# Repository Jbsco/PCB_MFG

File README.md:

# PCB_MFG

This repository was created for working with and improving the on-campus PCB design and production process using open-source software resources as well as physical resources and space provided by the University of Colorado Boulder and Colorado Mesa University Partnership Program on the Colorado Mesa University campus. These resources are made available to students and faculty alike.

## Introduction

PCB production is in the process of being made more accessible to students and faculty. Desktop CNC machines are available in labs at Confluence Hall which have the capacity to produce good quality single-sided designs, as well as double-sided designs (with some additional effort), with low/no cost for students and faculty. Efforts have been made to reduce complexity and improve ease-of-use by developing a consistent and repeatable process that produces usable results in a shorter time-frame than ordering from third-party prototyping services.

## Participation

Student and faculty participation in this repository is encouraged! Please check the  and <a href="../../issues">Issues</a> pages to learn about proposed changes and additions. Your engagement in development of this process is welcome. Feedback is also appreciated!
A great way to get started with new commits is to fork this repository, make your changes, and create a pull request to merge changes back into the main branch (pending approval). [Workflow actions](https://github.com/Jbsco/PCB_MFG/actions) are enabled to help enforce spell checking, this uses the [Check-Spelling](https://github.com/marketplace/actions/check-spelling) action.

## Hardware Used

The CNC machines located in Confluence Hall labs are being made available for specific projects by faculty permission, and may be made more widely available in the future. Discuss access with faculty and ensure thorough understanding of the equipment, materials, and lab policies before use - you will gain valuable assistance and knowledge to improve your results and ensure that these resources remain effective and safe for use.

### Genmitsu 3018 Pro Desktop CNC Machines

A 3D-printable fixture which fits 100x70mm copper-clad boards is provided as an STL file in this repository. This was designed specifically for this CNC machine and this process. It provides an easy clamping method with consistent repeatability.

## Software Used

The following software is available on GitHub or their respective web sites, and each were found to be effective for each part of the process detailed within this repository. System compatibility and ease-of-use were priorities, as was open-source status.

* [**Candle**: CNC control and heightmapping software (Windows or Linux)](https://github.com/Denvi/Candle)

* **FlatCAM**: Gerber & Excellon intake, toolpathing, and Gcode output (Windows, Linux, MacOSX) ***comprehensive alternative to Inkscape & jscut***
  * [FlatCAM BitBucket](https://bitbucket.org/jpcgt/flatcam/src/master)
  * [FlatCAM Docs](http://flatcam.org)

* **KiCAD**: Schematic & PCB design software, simulation, Gerber & SVG output (Docker, Windows, Linux, MacOSX)
  * [KiCAD GitHub](https://github.com/KiCad)
  * [KiCAD GitLab](https://gitlab.com/kicad)

Originally, Inkscape and jscut were used to create Gcode files using SVGs, rather than Gerber files. This tested poorly among students, so FlatCAM is preferred, but this process is retained below the current process for posterity.

* **jscut**: SVG intake, toolpathing, and GCode output (in-browser)[
  * [jscut GitHub](https://github.com/tbfleming/jscut)
  * [jscut](https://jscut.org) 
* [**Inkscape**: SVG preparation for jscut (Windows, Linux, MacOSX) ](https://github.com/inkscape/inkscape)

## Process

It is recommended to have access to the above software. As they have their own release channels please refer to their documentation. Generally, Candle, FlatCAM, and KiCAD are installed software, and releases are available from their respective sites. Linux installs for common distributions are often available.

Arch Linux users are recommended to install `candle-bin` from the AUR using `yay`, while FlatCAM runs from source using `python FlatCAM.py` after installing dependencies (`python-vispy` 0.7 or lower is needed. FlatCAM can also be installed as `flatcam-git` from the AUR using `yay`, but the dependency `python-svg.path` may need to be installed with the `--mflags "--nocheck"` flags in order to bypass failed tests), and KiCAD is available using `pacman -Syu kicad` and KiCAD libraries using `pacman -Syu --asdeps kicad-library kicad-library-3d`.

Drivers for the 3018 CNC machine may need to be installed for communication through Candle, these may be found on the Sainsmart site.

Additional documentation (including general usage guides, tips, and tricks) for each application used in this process will be linked within this repo.

## Tutorials

* [Using KiCAD](Documentation/using_KiCAD.md)
* [Using FlatCAM](Documentation/using_FlatCAM.md)
* [Using Candle](Documentation/using_Candle.md)

Originally, Inkscape and jscut were used to create Gcode files using SVGs, rather than Gerber files. This tested poorly among students, so FlatCAM is preferred, but this process is retained here for posterity.

* [Using Inkscape and jscut](Documentation/using_Inkscape_JSCut.md)

## Heightmap Modeling
As a Fall 2023 Intro to Probability Theory final project, a dataset was built from Candle heightmaps and various conclusions were drawn from observations and analysis of this data. Data was interpreted using the MATLAB scripts included in this repository. The resultant report and supporting materials are included in [Reports](/Reports/).

The resultant model heightmap, which is based on the mean data, is available at [/Reports/Code/bootModel.map](/Reports/Code/bootModel.map). This heightmap may prove more useful as the dataset grows.

In the future, other students and faculty will have the opportunity to contribute to the dataset and assist in refining the model.

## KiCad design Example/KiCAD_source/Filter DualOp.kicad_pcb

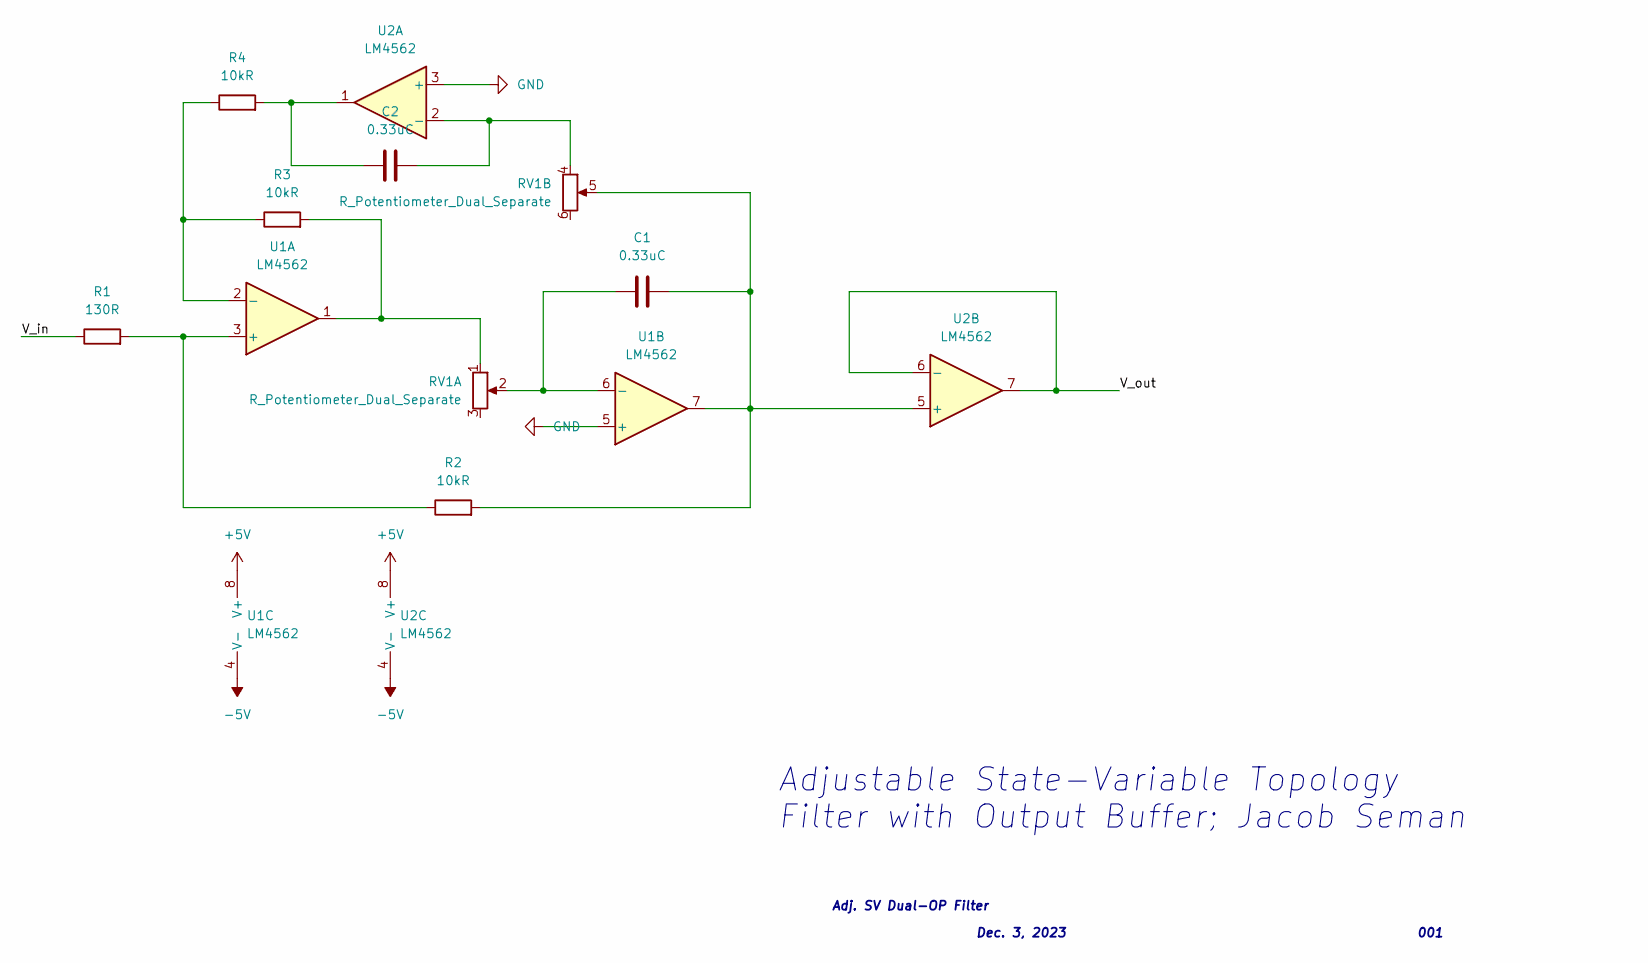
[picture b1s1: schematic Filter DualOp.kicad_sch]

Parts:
C1, C2: 0.33uC; C_Disc_D5.0mm_W2.5mm_P2.50mm
R1: 130R; R_Axial_DIN0207_L6.3mm_D2.5mm_P2.54mm_Vertical
R2, R3, R4: 10kR; R_Axial_DIN0207_L6.3mm_D2.5mm_P2.54mm_Vertical
RV1: R_Potentiometer_Dual_Separate; Potentiometer_Alps_RK097_Dual_Horizontal
U1, U2: LM4562; DIP-8_W7.62mm

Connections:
+5V: U1.8 (V+), U2.8 (V+)
-5V: U1.4 (V-), U2.4 (V-)
/V_in: R1.1
/V_out: U2.6 (-), U2.7
GND: U1.5 (+), U2.3 (+)
unnamed: C1.1, RV1.2, U1.6 (-)
unnamed: C1.2, R2.2, RV1.5, U1.7, U2.5 (+)
unnamed: C2.1, R4.2, U2.1
unnamed: C2.2, RV1.4, U2.2 (-)
unnamed: R1.2, R2.1, U1.3 (+)
unnamed: R3.1, R4.1, U1.2 (-)
unnamed: R3.2, RV1.1, U1.1

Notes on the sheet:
Dec. 3, 2023
Adj. SV Dual-OP Filter
Adjustable State-Variable Topology Filter with Output Buffer; Jacob Seman
001

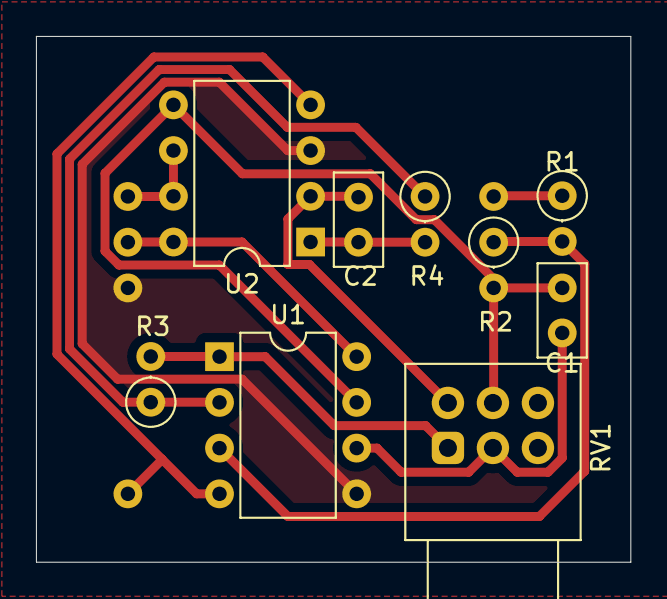
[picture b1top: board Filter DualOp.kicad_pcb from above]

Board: 2 copper layers, 33.0 x 29.2 mm, 9 parts (0 on the bottom side), 11 nets.

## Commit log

2023-12-06 initializing repository
2023-12-06 init organization
2023-12-07 Update README.md with primary intent, tools & software used, and a general procees
2023-12-07 organization, included example circuit SPICE simulations
2023-12-07 renaming images for relative linking in README
2023-12-07 added SVG preview for relative linking in README
2023-12-07 improved SVG preview for relative linking in README
2023-12-07 added images for relative linking in README
2023-12-07 Update README.md with relative links to imagery
2023-12-07 Update README.md, minor typos
2023-12-07 Update README.md, minor clarifications
2023-12-07 Update README.md, minor clarifications, elaboration on provided fixture
2023-12-07 removed external PDF documents cited in probability reports
2023-12-07 cleaned up extraneous files in reports folder
2023-12-07 Update README.md, minor typo
2023-12-07 Update README.md, minor formatting
2023-12-07 Update README.md, clarification on heightmap routine
2023-12-07 Update README.md, minor clarification in heightmapping
2023-12-07 Update README.md, added Flatcam as comprehensive alternative to Inkscape and JScut
2023-12-07 Update README.md, minor font adjustment
2023-12-07 Update README.md, additional Flatcam links
2023-12-07 Update README.md, minor additions regarding Flatcam and common procedures
2023-12-07 Update README.md, elaboration on Flatcam vs Inkscape/JScut comparison
2023-12-07 added gerber output and gcode/drill outputs from Flatcam testing
2023-12-07 Update README.md, added section on heightmap modelling project
2023-12-07 Update README.md, minor punctuation
2023-12-07 updated example project KiCAD project files
2023-12-07 added relevant Inkscape keybind shortcuts
2023-12-07 updated KiCAD project files
2023-12-08 added FlatCAM files, nearing completion of FlatCAM process testing
2023-12-08 Update README.md, added process instructions for FlatCAM
2023-12-08 Update README.md, Excellon intake in FlatCAM description
2023-12-08 Update README.md, minor process introduction changes to reflect FlatCAM use
2023-12-08 updated with FlatCAM images
2023-12-08 updated Candle images
2023-12-08 Update README.md, added FlatCAM relative links to images
2023-12-08 updated example filter design report
2023-12-08 Update README.md, mention of different continuity probe control board labels
2023-12-08 Update README.md, added instruction for switching from schematic to PCB editor
    Addresses #2.
2023-12-08 added Arch Linux install notes
2023-12-08 added KiCAD library depoendencies for Arch Linux install
2023-12-09 Update README.md, cleaning up software installation notes
2023-12-10 added model heightmap "bootModel.map" and additional report materials
2023-12-11 added preprocessor selection note
2023-12-11 Update README.md, updated to reflect preprocessor selection
2023-12-14 Update README.md - included link to model heightmap
2024-01-12 Update README.md: minor terminology fix
2024-02-23 Update README.md
    Addressing #7
2024-03-01 initializing supplementary markdown documentation for KiCAD, FlatCAM, & Candle per issue #9, discussion #8
2024-03-01 added Participation section to main README
2024-03-06 Create spellcheck.yml
    creating workflow for spellcheck
2024-03-06 creating workflow for spellcheck
2024-03-06 adjusting workflow for spellcheck
2024-03-08 Adding 15 degree V-bit
2024-03-09 Updated Readme to refer to new FlatCAM tools import file
2024-03-20 Added workflow action passing/failing badge to README.md
2024-03-20 Update workflow
2024-03-21 md-ify it
2024-03-21 consistent capatilization
2024-03-21 move docs over
2024-03-21 i am dumb
2024-03-21 restored some image formatting such as center and width not available in markdown
2024-04-01 Update using_FlatCAM.md
    Update to use the right slicer
2026-02-05 Update KiCad documentation and add images
2026-02-05 Reorganize KiCad documentation
2026-02-06 Update FlatCAM documentation and add images
2026-02-06 Update FlatCAM documentation and add images (2)
2026-02-06 Update FlatCAM documentation - Tips to install in Linux
2026-02-12 Update Candle documentation
2026-02-12 Update Candle documentation (2)
